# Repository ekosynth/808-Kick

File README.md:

# 808-Kick
This project is an adaptation of bananeurysm/jmej's 808 Kick drum circuit. It takes the idea and refines the board layout slightly.

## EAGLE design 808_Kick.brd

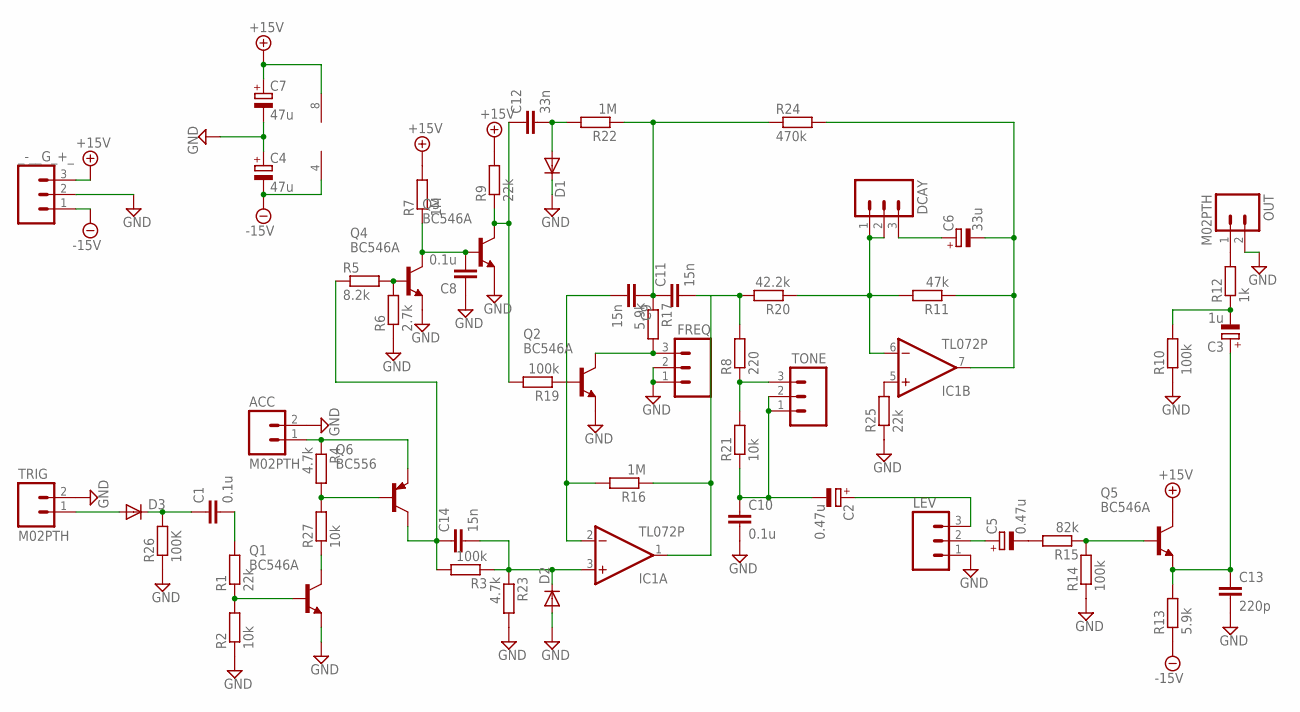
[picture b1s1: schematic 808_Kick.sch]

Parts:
ACC: M02PTH; 1X02
C1, C8, C10: 0.1u; C025-024X044
C2, C5: 0.47u; E2,5-6E
C3: 1u; E2,5-6E
C4, C7: 47u; E2,5-6E
C6: 33u; E2,5-6E
C9, C11, C14: 15n; C025-024X044
C12: 33n; C025-024X044
C13: 220p; C025-024X044
D1, D2, D3: DIODE-D-2.5; D-2.5
DCAY: M03PTH; 1X03
FREQ: M03PTH; 1X03
IC1: TL072P; DIL08
LEV: M03PTH; 1X03
OUT: M02PTH; 1X02
Q1, Q2, Q3, Q4, Q5: BC546A; TO92-EBC
Q6: BC556; TO92-EBC
R1, R9, R25: 22k; 0207/2V
R2, R21, R27: 10k; 0207/2V
R3, R10, R14, R19: 100k; 0207/2V
R4, R23: 4.7k; 0207/2V
R5: 8.2k; 0207/2V
R6: 2.7k; 0207/2V
R7, R16, R22: 1M; 0207/2V
R8: 220; 0207/2V
R11: 47k; 0207/2V
R12: 1k; 0207/2V
R13, R17: 5.9k; 0207/2V
R15: 82k; 0207/2V
R20: 42.2k; 0207/2V
R24: 470k; 0207/2V
R26: 100K; 0207/2V
TONE: M03PTH; 1X03
TRIG: M02PTH; 1X02
_-__G_+_: M03PTH; 1X03

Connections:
+15V: C7.+, IC1.8 (V+), Q5.C, R7.2, R9.2, _-__G_+_.3
-15V: C4.-, IC1.4 (V-), R13.1, _-__G_+_.1
FREQ: C11.2, IC1.1 (OUT), R8.2, R16.1, R20.2
GND: ACC.2, C4.+, C7.-, C8.1, C10.2, C13.2, D1.C, D2.A, FREQ.1, FREQ.2, LEV.1, OUT.2, Q1.E, Q2.E, Q3.E, Q4.E, R2.1, R6.1, R10.1, R14.1, R23.2, R25.1, R26.1, TRIG.2, _-__G_+_.2
LEV: C5.+, LEV.2
unnamed: Q4.B, R5.2, R6.2
unnamed: C8.2, Q3.B, Q4.C, R7.1
unnamed: Q5.B, R14.2, R15.1
unnamed: Q2.B, R19.1
unnamed: IC1.5 (+IN), R25.2
unnamed: Q6.B, R4.2, R27.2
unnamed: C1.2, R1.2
unnamed: C9.2, IC1.2 (-IN), R16.2
unnamed: C3.-, R10.2, R12.1
unnamed: C5.-, R15.2
unnamed: C9.1, C11.1, R17.1, R22.1, R24.1
unnamed: OUT.1, R12.2
unnamed: FREQ.3, Q2.C, R17.2
unnamed: C14.2, D2.C, IC1.3 (+IN), R3.1, R23.1
unnamed: C14.1, Q6.C, R3.2, R5.1
unnamed: ACC.1, Q6.E, R4.1
unnamed: C3.+, C13.1, Q5.E, R13.2
unnamed: C2.+, LEV.3
unnamed: C6.-, IC1.7 (OUT), R11.1, R24.2
unnamed: Q1.C, R27.1
unnamed: C6.+, DCAY.3
unnamed: DCAY.1, DCAY.2, IC1.6 (-IN), R11.2, R20.1
unnamed: R8.1, R21.2, TONE.3
unnamed: Q1.B, R1.1, R2.2
unnamed: C2.-, C10.1, R21.1, TONE.1, TONE.2
unnamed: C12.1, Q3.C, R9.1, R19.2
unnamed: C12.2, D1.A, R22.2
unnamed: C1.1, D3.C, R26.2
unnamed: D3.A, TRIG.1

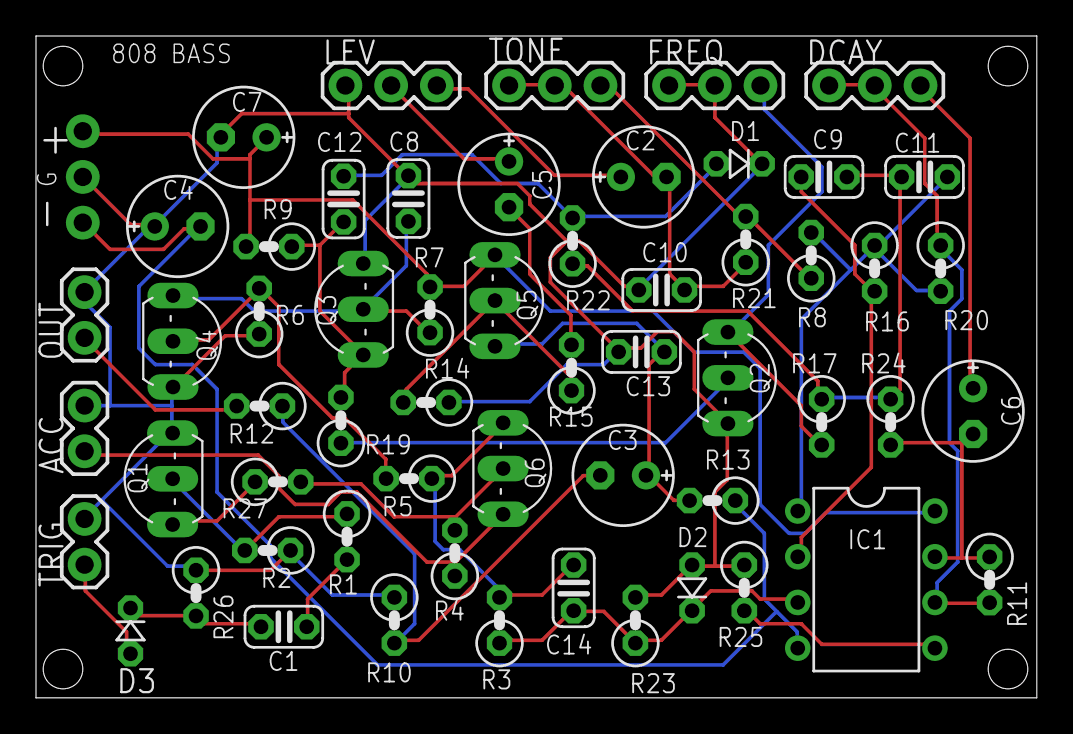
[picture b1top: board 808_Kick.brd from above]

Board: 2 copper layers, 55.6 x 36.8 mm, 58 parts (1 on the bottom side), 34 nets.

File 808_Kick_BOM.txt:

Partlist exported from C:/Users/Jack/Documents/GitHub/808-Kick/808_Kick.sch at 08/07/2015 18:48

Part     Value  Device          Package      Description                          
ACC      M02PTH M02PTH          1X02         Standard 2-pin 0.1" header. Use with 
C1       0.1u   C-EU025-024X044 C025-024X044 CAPACITOR, European symbol           
C2       0.47u  CPOL-EUE2,5-6E  E2,5-6E      POLARIZED CAPACITOR, European symbol 
C3       1u     CPOL-EUE2,5-6E  E2,5-6E      POLARIZED CAPACITOR, European symbol 
C4       47u    CPOL-EUE2,5-6E  E2,5-6E      POLARIZED CAPACITOR, European symbol 
C5       0.47u  CPOL-EUE2,5-6E  E2,5-6E      POLARIZED CAPACITOR, European symbol 
C6       33u    CPOL-EUE2,5-6E  E2,5-6E      POLARIZED CAPACITOR, European symbol 
C7       47u    CPOL-EUE2,5-6E  E2,5-6E      POLARIZED CAPACITOR, European symbol 
C8       0.1u   C-EU025-024X044 C025-024X044 CAPACITOR, European symbol           
C9       15n    C-EU025-024X044 C025-024X044 CAPACITOR, European symbol           
C10      0.1u   C-EU025-024X044 C025-024X044 CAPACITOR, European symbol           
C11      15n    C-EU025-024X044 C025-024X044 CAPACITOR, European symbol           
C12      33n    C-EU025-024X044 C025-024X044 CAPACITOR, European symbol           
C13      220p   C-EU025-024X044 C025-024X044 CAPACITOR, European symbol           
C14      15n    C-EU025-024X044 C025-024X044 CAPACITOR, European symbol           
D1       1N4148 DIODE-D-2.5     D-2.5        DIODE                                
D2       1N4148 DIODE-D-2.5     D-2.5        DIODE                                
D3       1N914  DIODE-D-2.5     D-2.5        DIODE                                
DCAY            M03PTH          1X03         Header 3                             
FREQ            M03PTH          1X03         Header 3                             
IC1      TL072P TL072P          DIL08        OP AMP                               
LEV             M03PTH          1X03         Header 3                             
OUT      M02PTH M02PTH          1X02         Standard 2-pin 0.1" header. Use with 
Q1       BC546A BC546A          TO92-EBC     NPN Transistor                       
Q2       BC546A BC546A          TO92-EBC     NPN Transistor                       
Q3       BC546A BC546A          TO92-EBC     NPN Transistor                       
Q4       BC546A BC546A          TO92-EBC     NPN Transistor                       
Q5       BC546A BC546A          TO92-EBC     NPN Transistor                       
Q6       BC556  BC556           TO92-EBC     PNP Transistror                      
R1       22k    R-EU_0207/2V    0207/2V      RESISTOR, European symbol            
R2       10k    R-EU_0207/2V    0207/2V      RESISTOR, European symbol            
R3       100k   R-EU_0207/2V    0207/2V      RESISTOR, European symbol            
R4       4.7k   R-EU_0207/2V    0207/2V      RESISTOR, European symbol            
R5       8.2k   R-EU_0207/2V    0207/2V      RESISTOR, European symbol            
R6       2.7k   R-EU_0207/2V    0207/2V      RESISTOR, European symbol            
R7       1M     R-EU_0207/2V    0207/2V      RESISTOR, European symbol            
R8       220    R-EU_0207/2V    0207/2V      RESISTOR, European symbol            
R9       22k    R-EU_0207/2V    0207/2V      RESISTOR, European symbol            
R10      100k   R-EU_0207/2V    0207/2V      RESISTOR, European symbol            
R11      47k    R-EU_0207/2V    0207/2V      RESISTOR, European symbol            
R12      1k     R-EU_0207/2V    0207/2V      RESISTOR, European symbol            
R13      5.9k   R-EU_0207/2V    0207/2V      RESISTOR, European symbol            
R14      100k   R-EU_0207/2V    0207/2V      RESISTOR, European symbol            
R15      82k    R-EU_0207/2V    0207/2V      RESISTOR, European symbol            
R16      1M     R-EU_0207/2V    0207/2V      RESISTOR, European symbol            
R17      5.9k   R-EU_0207/2V    0207/2V      RESISTOR, European symbol            
R19      100k   R-EU_0207/2V    0207/2V      RESISTOR, European symbol            
R20      42.2k  R-EU_0207/2V    0207/2V      RESISTOR, European symbol            
R21      10k    R-EU_0207/2V    0207/2V      RESISTOR, European symbol            
R22      1M     R-EU_0207/2V    0207/2V      RESISTOR, European symbol            
R23      4.7k   R-EU_0207/2V    0207/2V      RESISTOR, European symbol            
R24      470k   R-EU_0207/2V    0207/2V      RESISTOR, European symbol            
R25      22k    R-EU_0207/2V    0207/2V      RESISTOR, European symbol            
R26      100K   R-EU_0207/2V    0207/2V      RESISTOR, European symbol            
R27      10k    R-EU_0207/2V    0207/2V      RESISTOR, European symbol            
TONE            M03PTH          1X03         Header 3                             
TRIG     M02PTH M02PTH          1X02         Standard 2-pin 0.1" header. Use with 
_-__G_+_        M03PTH          1X03         Header 3

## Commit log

2015-06-04 :octocat: Added .gitattributes & .gitignore files
2015-06-08 808 Update and board added
2015-06-09 Updated board
    Needs all layer 25 adding to silkscreen (layer 21)
2015-06-09 Updated board
2015-06-10 Moved all component names to layer 21
2015-06-12 Board Completed
    Board Complete - Gerber files generated
2015-06-12 Added info template to schematic

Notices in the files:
parts and their libraries:
SparkFun-Connectors: Licensing: Creative Commons ShareAlike 4.0 International - https://creativecommons.org/licenses/by-sa/4.0
